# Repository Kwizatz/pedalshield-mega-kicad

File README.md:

# pedalshield-mega-kicad

Native KiCAD files for ElecroSmash PedalShield MEGA.

The purpose for this repository is to reconstruct the source files for the PCB, so it is easier to modify and generate gerber files for PCB manufacture.

Libraries and Modules have been added to the repo to keep it as self contained as possible and the project _should_ load with no errors on KiCAD 6.0.

Please feel free to fork and submit pull requests if you see any room of improvement because I am not really an electronics engineer, I am learning as I go.

Enjoy!

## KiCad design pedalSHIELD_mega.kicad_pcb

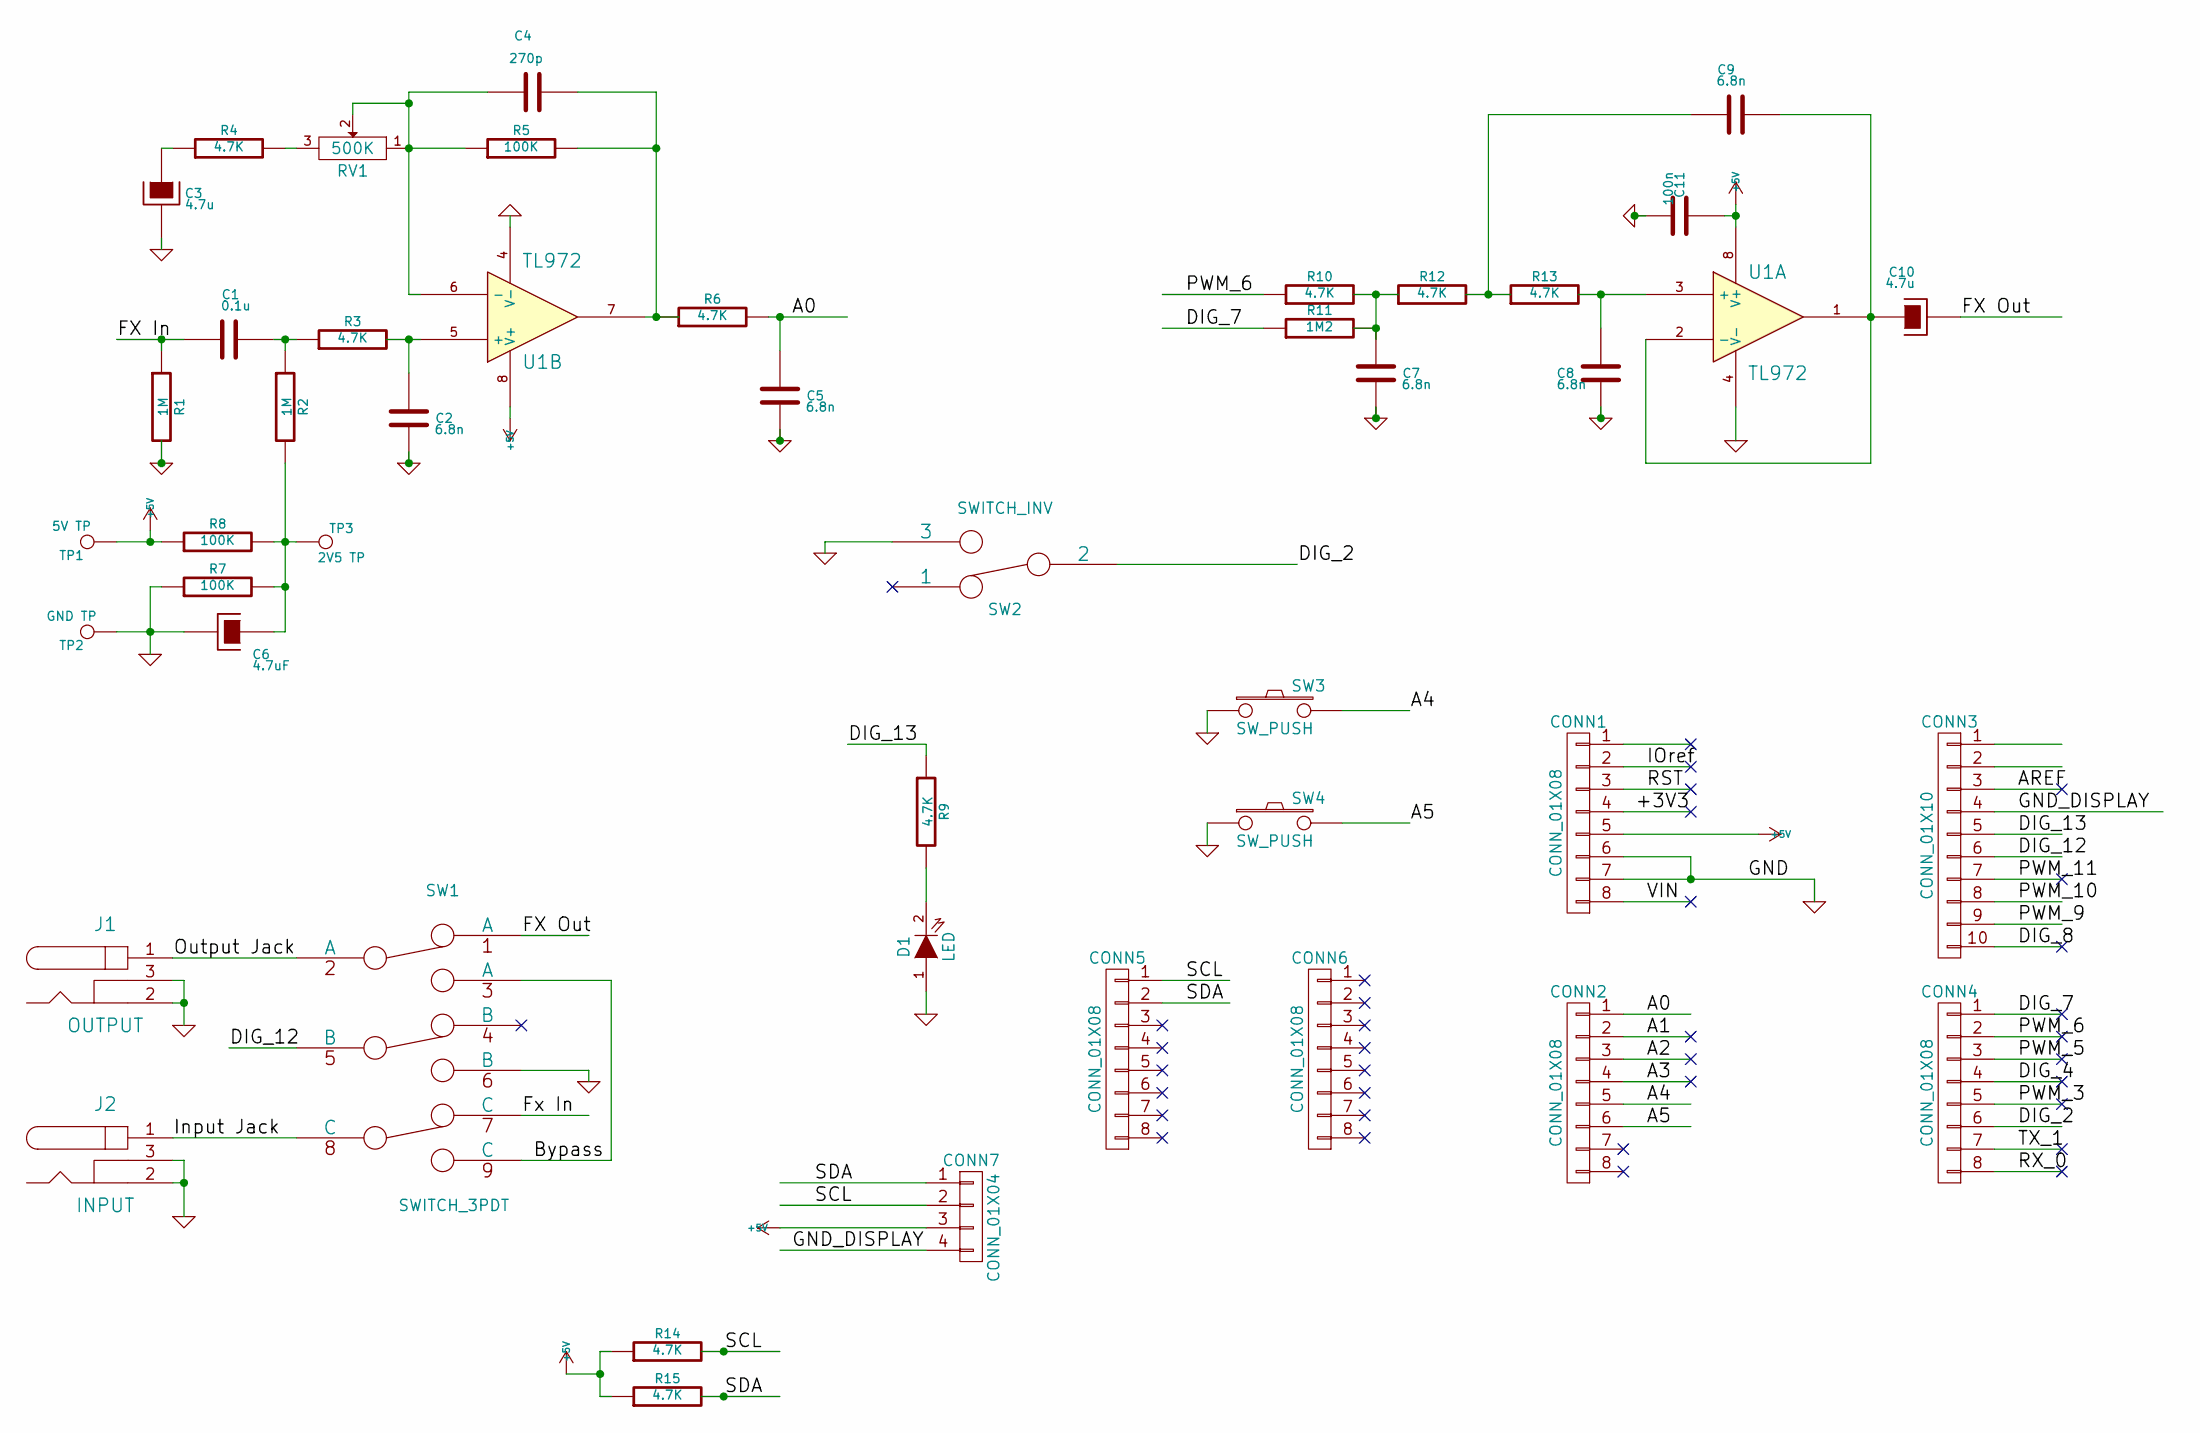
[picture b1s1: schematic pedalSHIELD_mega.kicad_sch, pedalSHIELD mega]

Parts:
C1: 0.1u; C_Rect_L7_W2_P5
C2, C5, C7, C8, C9: 6.8n; C_Rect_L7_W2_P5
C3: 4.7u; C_Radial_D5_L11_P2.5
C4: 270p; C_Rect_L7_W2_P5
C6: 4.7uF; C_Radial_D5_L11_P2
C10: 4.7u; C_Radial_D5_L11_P2
C11: 100n; C_Rect_L7_W2_P5
CONN1, CONN4: CONN_01X08; Pin_Header_Straight_1x08
CONN2, CONN5, CONN6: CONN_01X08; Pin_Header_Straight_1x08_Pitch2.54mm
CONN3: CONN_01X10; Pin_Header_Straight_1x10
CONN7: CONN_01X04; Pin_Header_Straight_1x04_Pitch2.54mm
D1: LED; LED-3MM
J1: OUTPUT; JACK_AUDIO
J2: INPUT; JACK_AUDIO
R1, R2: 1M; R3
R3, R4, R6, R9, R10, R12, R13: 4.7K; R3
R5, R7, R8: 100K; R3
R11: 1M2; R3
R14, R15: 4.7K; R_Axial_DIN0207_L6.3mm_D2.5mm_P7.62mm_Horizontal
RV1: 500K; POT_LOG
SW1: SWITCH_3PDT; 3PDT_psuno
SW2: SWITCH_INV; SW_SPDT
SW3, SW4: SW_PUSH; push_buttom_psuno
TP1: 5V TP; PINTST
TP2: GND TP; PINTST
TP3: 2V5 TP; PINTST
U1: TL972; PDIP-8

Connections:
+5V: C11.1, CONN1.5, CONN7.3, R8.1, R14.1, R15.1, TP1.1, U1.8 (V+)
/+3V3: CONN1.4
/A0: C5.2, CONN2.1, R6.2
/A1: CONN2.2
/A2: CONN2.3
/A3: CONN2.4
/A4: CONN2.5, SW3.2
/A5: CONN2.6, SW4.2
/AREF: CONN3.3
/Bypass: SW1.3 (A), SW1.9 (C)
/DIG_2: CONN4.6, SW2.2
/DIG_4: CONN4.4
/DIG_7: CONN4.1, R11.1
/DIG_8: CONN3.10
/DIG_12: CONN3.6, SW1.5 (B)
/DIG_13: CONN3.5, R9.1
/FX In: C1.1, R1.1
/FX Out: C10.2, SW1.1 (A)
/Fx In: SW1.7 (C)
/GND_DISPLAY: CONN3.4, CONN7.4
/IOref: CONN1.2
/Input Jack: J2.1, SW1.8 (C)
/Output Jack: J1.1, SW1.2 (A)
/PWM_3: CONN4.5
/PWM_5: CONN4.3
/PWM_6: CONN4.2, R10.1
/PWM_9: CONN3.9
/PWM_10: CONN3.8
/PWM_11: CONN3.7
/RST: CONN1.3
/RX_0: CONN4.8
/SCL: CONN5.1, CONN7.2, R14.2
/SDA: CONN5.2, CONN7.1, R15.2
/TX_1: CONN4.7
/VIN: CONN1.8
GND: C2.1, C3.2, C5.1, C6.2, C7.1, C8.2, C11.2, CONN1.6, CONN1.7, D1.1 (A), J1.2, J1.3, J2.2, J2.3, R1.2, R7.1, SW1.6 (B), SW2.3, SW3.1, SW4.1, TP2.1, U1.4 (V-)
unnamed: C1.2, R2.1, R3.1
unnamed: C2.2, R3.2, U1.5 (+)
unnamed: C3.1, R4.1
unnamed: C4.1, R5.1, RV1.1, RV1.2, U1.6 (-)
unnamed: C4.2, R5.2, R6.1, U1.7
unnamed: C6.1, R2.2, R7.2, R8.2, TP3.1
unnamed: C7.2, R10.2, R11.2, R12.1
unnamed: C8.1, R13.2, U1.3 (+)
unnamed: C9.1, R12.2, R13.1
unnamed: C9.2, C10.1, U1.1, U1.2 (-)
unnamed: D1.2 (K), R9.2
unnamed: R4.2, RV1.3

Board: 2 copper layers, 46 parts (0 on the bottom side), 30 nets, no tracks yet.

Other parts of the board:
Arduino Mega Shield: VAL**; ARDUINO MEGA SHIELD

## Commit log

2022-09-29 Added original files from electrosmash.com, no changes yet.
2022-09-29 Fixing/adding library paths and missing PCB footprints
